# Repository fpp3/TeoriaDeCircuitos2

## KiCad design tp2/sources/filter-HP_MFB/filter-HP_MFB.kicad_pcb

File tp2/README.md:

# TC2 - Trabajo Práctico Nº 2: Caracterización de Filtro Activo (Sección 2.1.5)

Aplicación web interactiva y ultrarrápida diseñada específicamente para la toma de datos de laboratorio, cálculo automático de tolerancias/errores, trazado de curvas y exportación para el informe de la **Sección 2.1.5** del TP2 de **Teoría de Circuitos II (UTN FRC)**.

---

## 🚀 Cómo ejecutar la aplicación

Podés iniciarla con Python (abre el navegador automáticamente):

```bash
python3 run_app.py
```

O también podés abrir directamente en tu navegador el archivo:
```bash
app/index.html
```

> **Nota:** La aplicación es **100% offline y autónoma** (las librerías están incluidas localmente en `app/lib/`), por lo que podés usarla en el laboratorio sin conexión a internet ni WiFi.

---

## ⚡ Características principales

### 1. Pensada para mediciones de tensión sobre resistencias y puntos de prueba
Tal como se trabaja en el banco de laboratorio, **no hace falta abrir el circuito para intercalar un amperímetro**:
- **Entrada ($I_{in}$):** Se ingresa la caída de tensión medida sobre la resistencia de shunt de entrada ($V_{Rshunt,in}$), y la app calcula $I_{in} = \frac{V_{Rshunt,in}}{R_{shunt,in}}$.
- **Etapa 1 ($V_{E1}$):** Medición de tensión en la salida del restador (pin 8 de U1C) respecto a GND.
- **Etapa 2 ($V_{filtro}$):** Medición de tensión en la salida del Sallen-Key (pin 14 de U1D) respecto a GND.
- **Etapa 3 ($I_{out}$ hacia PLC):** Permite elegir cómo se midió la salida:
  1. *Caída sobre $R_{carga}$ ($V_{Rcarga}$):* $I_{out} = \frac{V_{Rcarga}}{R_{carga}}$ (Recomendado).
  2. *Tensión en colector de Q1 ($V_C$ a GND):* $V_{Rcarga} = V_{CC} - V_C \implies I_{out} = \frac{V_{Rcarga}}{R_{carga}}$.
  3. *Tensión en emisor de Q1 ($V_E$ sobre $R_{shunt,out}$):* $I_E = \frac{V_E}{R_{shunt,out}} \implies I_{out} = \alpha \cdot I_E$.
  4. *Medición directa con miliamperímetro* ($I_{out}$ en mA).

### 2. Calibración real de componentes
Permite ingresar los valores reales medidos con multímetro de:
- $R_{shunt,in}$ (nominal 250 $\Omega$)
- $R_{shunt,out}$ (nominal 250 $\Omega$)
- $R_{carga}$ (nominal 250 $\Omega$)
- $V_{CC}$ de fuente (nominal 24.0 V)
- $\beta$ estimado del transistor BC337 / 2N2222 (para evaluar el error teórico por corriente de base $\alpha = \frac{\beta}{\beta+1}$)

### 3. Caracterización Estática (Linealidad 4 a 20 mA)
- Puntos estándar de inyección: 4 mA, 8 mA, 12 mA, 16 mA y 20 mA (con posibilidad de agregar o quitar filas).
- Cálculo en tiempo real de errores relativos porcentuales de cada etapa.
- Regresión lineal por mínimos cuadrados ($I_{out} = m \cdot I_{in} + b$) y coeficiente $R^2$.
- Gráfico interactivo de la curva de transferencia $I_{out}$ vs $I_{in}$ superpuesto a la recta ideal.
- Gráfico de barras de distribución de errores por etapa.

### 4. Caracterización Dinámica (Bode 1 Hz a 100 Hz)
- Barrido de frecuencias con inyección senoidal + offset DC.
- Entrada de $V_{in}$ y $V_{out}$ (en $V_{pp}$ medidos con osciloscopio) y $\Delta t$ opcional para fase.
- Cálculo automático de ganancia $A_v$, magnitud en dB y comparación contra la curva teórica de Butterworth de 2º orden ($f_c = 10\text{ Hz}$):
  $$|H(jf)|_{\text{dB}} = -10 \log_{10}\left(1 + \left(\frac{f}{10}\right)^4\right)$$
- **Frecuencia de corte real a -3 dB:** Interpolación log-lineal automática del punto exacto donde la ganancia cruza $-3.01\text{ dB}$.
- **Atenuación exacta a 50 Hz:** Verificación del rechazo al ruido de red de 50 Hz (ideal $-27.97\text{ dB}$, atenuación $\sim 25\times$).
- **Pendiente asintótica (Roll-off):** Cálculo de la caída en dB/década en la banda de rechazo (ideal $-40\text{ dB/déc}$).
- Diagrama de Bode interactivo en escala logarítmica con curva teórica continua, marcadores experimentales y líneas guía.

### 5. Guardado, Carga y Exportación
- **Auto-guardado en LocalStorage:** Cualquier dato ingresado queda guardado automáticamente en el navegador; si recargás la página o cerrás la pestaña, nada se pierde.
- **Guardar / Cargar Sesión JSON:** Backup completo descargable en formato `.json` para archivar o compartir entre compañeros de grupo.
- **Exportación CSV:** Descarga directa de archivos `.csv` para procesar en Excel, Google Sheets, Python o MATLAB.
- **Generador de Tablas LaTeX:** Código fuente listo con formato `\begin{table}` y `tabular` para pegar en Overleaf.
- **Resumen Markdown:** Conclusiones y valores clave listos para el informe.
- **Exportación de Gráficos:** Botones para descargar las imágenes PNG en alta definición.
- **Botón "Cargar Demo":** Carga datos coherentes de simulación para verificar visualmente todo el funcionamiento.

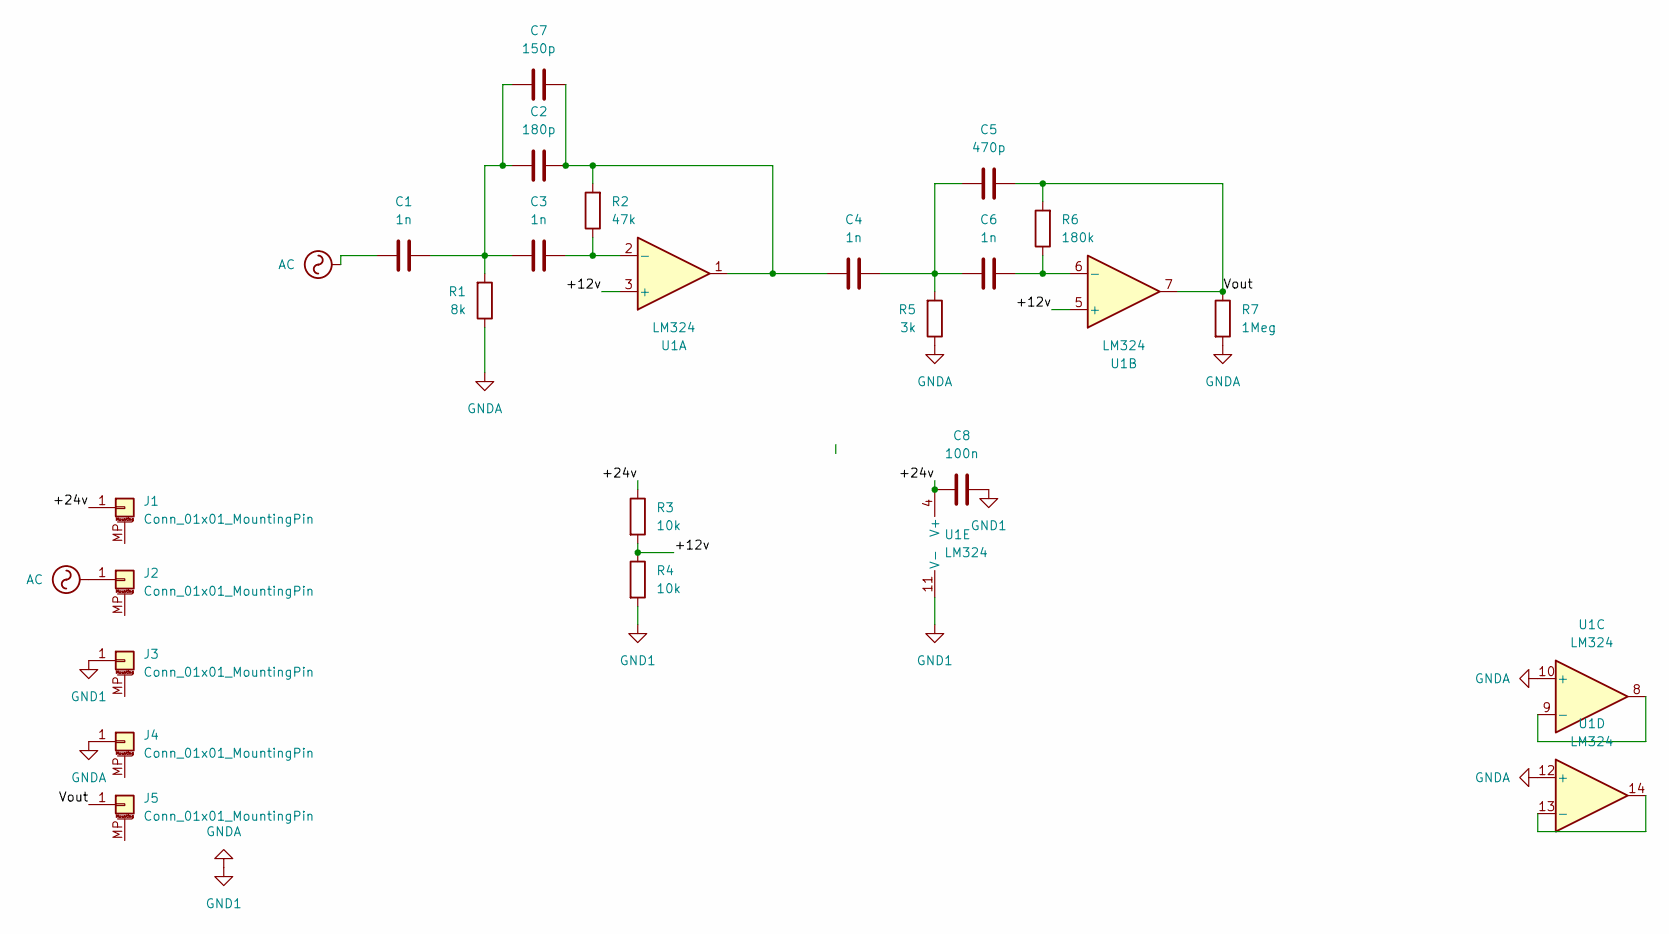
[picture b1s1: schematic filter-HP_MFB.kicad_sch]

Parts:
C1, C3, C4, C6: 1n; C_Disc_D5.0mm_W2.5mm_P5.00mm
C2: 180p; C_Disc_D5.0mm_W2.5mm_P5.00mm
C5: 470p; C_Disc_D5.0mm_W2.5mm_P5.00mm
C7: 150p; C_Disc_D5.0mm_W2.5mm_P5.00mm
C8: 100n; C_Disc_D5.0mm_W2.5mm_P5.00mm
J1, J2, J3, J4, J5: Conn_01x01_MountingPin; TestPoint_Pad_4.0x4.0mm
R1: 8k; R_Axial_DIN0207_L6.3mm_D2.5mm_P7.62mm_Horizontal
R2: 47k; R_Axial_DIN0207_L6.3mm_D2.5mm_P7.62mm_Horizontal
R3, R4: 10k; R_Axial_DIN0207_L6.3mm_D2.5mm_P7.62mm_Horizontal
R5: 3k; R_Axial_DIN0207_L6.3mm_D2.5mm_P7.62mm_Horizontal
R6: 180k; R_Axial_DIN0207_L6.3mm_D2.5mm_P7.62mm_Horizontal
R7: 1Meg; R_Axial_DIN0207_L6.3mm_D2.5mm_P7.62mm_Horizontal
U1: LM324; CERDIP-14_W7.62mm_SideBrazed_LongPads_Socket

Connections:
/+12v: R3.2, R4.1, U1.3 (+), U1.5 (+)
/+24v: C8.2, J1.1 (Pin_1_1), R3.1, U1.4 (V+)
/Vout: C5.1, J5.1 (Pin_1_1), R6.2, R7.1, U1.7
AC: C1.2, J2.1 (Pin_1_1)
GND1: C8.1, J3.1 (Pin_1_1), J4.1 (Pin_1_1), R1.1, R4.2, R5.1, R7.2, U1.10 (+), U1.11 (V-), U1.12 (+)
unnamed: C1.1, C2.2, C3.2, C7.2, R1.2
unnamed: C2.1, C4.2, C7.1, R2.2, U1.1
unnamed: C4.1, C5.2, C6.2, R5.2
unnamed: C3.1, R2.1, U1.2 (-)
unnamed: C6.1, R6.1, U1.6 (-)
unnamed: U1.8, U1.9 (-)
unnamed: U1.13 (-), U1.14

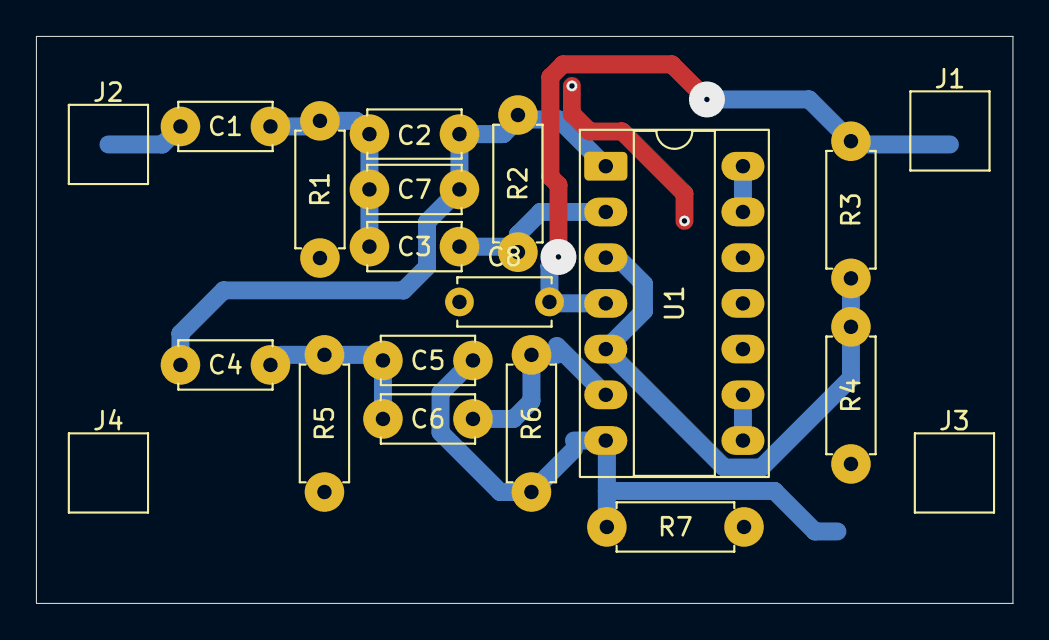
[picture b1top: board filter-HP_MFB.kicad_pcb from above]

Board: 2 copper layers, 54.2 x 31.5 mm, 21 parts (1 on the bottom side), 12 nets.

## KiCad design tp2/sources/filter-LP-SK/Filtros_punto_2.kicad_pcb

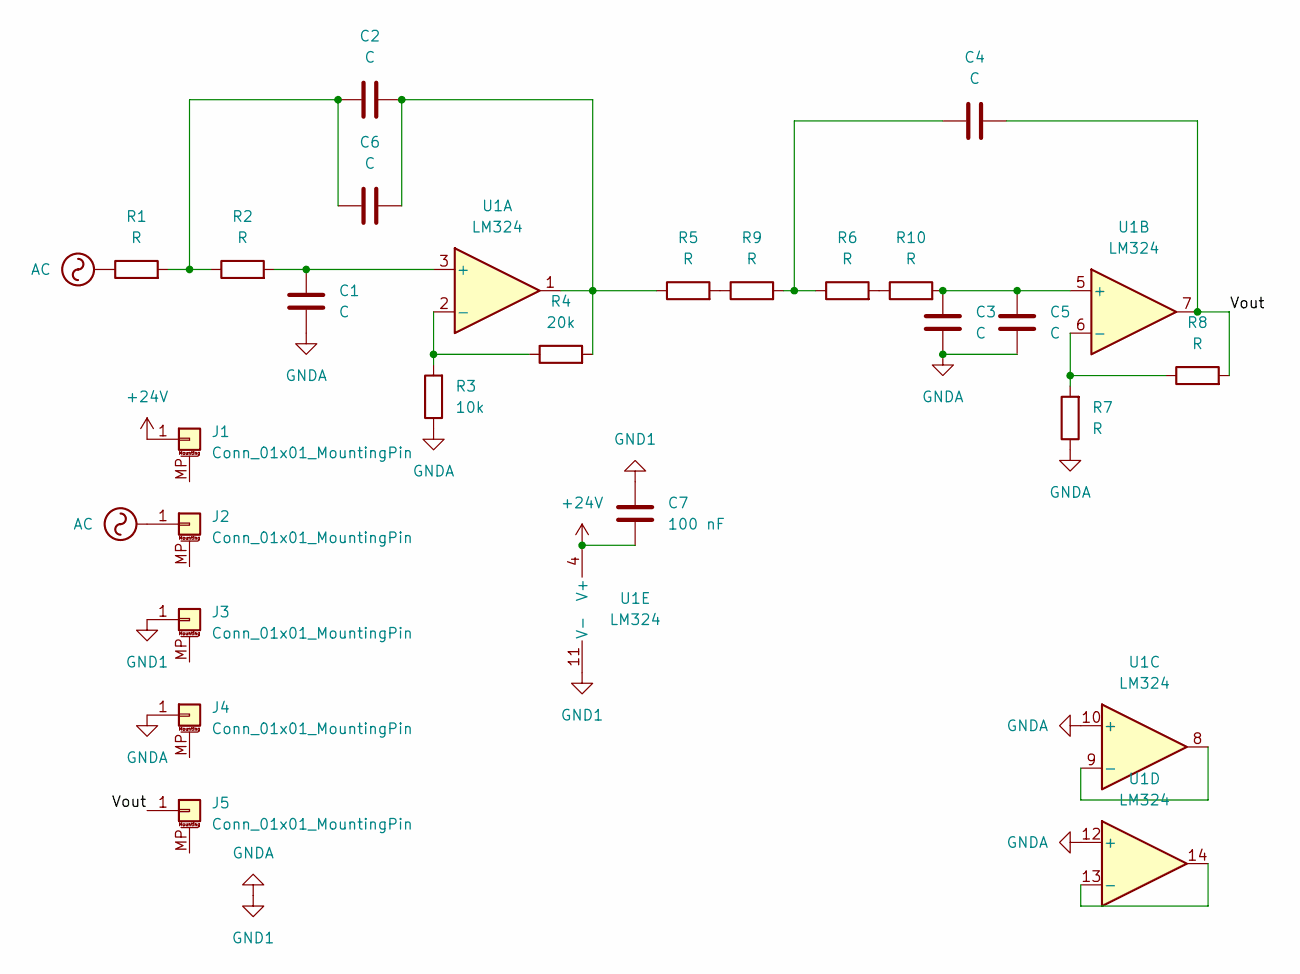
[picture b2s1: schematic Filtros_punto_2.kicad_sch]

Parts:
C1, C2, C3, C4, C5, C6: C; C_Disc_D5.0mm_W2.5mm_P5.00mm
C7: 100 nF; C_Disc_D5.0mm_W2.5mm_P5.00mm
J1, J2, J3, J4, J5: Conn_01x01_MountingPin; TestPoint_Pad_4.0x4.0mm
R1, R2, R5, R6, R7, R8, R9, R10: R; R_Axial_DIN0207_L6.3mm_D2.5mm_P7.62mm_Horizontal
R3: 10k; R_Axial_DIN0207_L6.3mm_D2.5mm_P7.62mm_Horizontal
R4: 20k; R_Axial_DIN0207_L6.3mm_D2.5mm_P7.62mm_Horizontal
U1: LM324; CERDIP-14_W7.62mm_SideBrazed_LongPads_Socket

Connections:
+24V: C7.2, J1.1 (Pin_1_1), U1.4 (V+)
/Vout: C4.1, J5.1 (Pin_1_1), R8.2, U1.7
AC: J2.1 (Pin_1_1), R1.1
GND1: C1.2, C3.2, C5.2, C7.1, J3.1 (Pin_1_1), J4.1 (Pin_1_1), R3.1, R7.1, U1.10 (+), U1.11 (V-), U1.12 (+)
unnamed: C2.1, C6.2, R4.2, R5.1, U1.1
unnamed: C2.2, C6.1, R1.2, R2.1
unnamed: C4.2, R6.1, R9.2
unnamed: R5.2, R9.1
unnamed: R6.2, R10.1
unnamed: C1.1, R2.2, U1.3 (+)
unnamed: R3.2, R4.1, U1.2 (-)
unnamed: C3.1, C5.1, R10.2, U1.5 (+)
unnamed: R7.2, R8.1, U1.6 (-)
unnamed: U1.8, U1.9 (-)
unnamed: U1.13 (-), U1.14

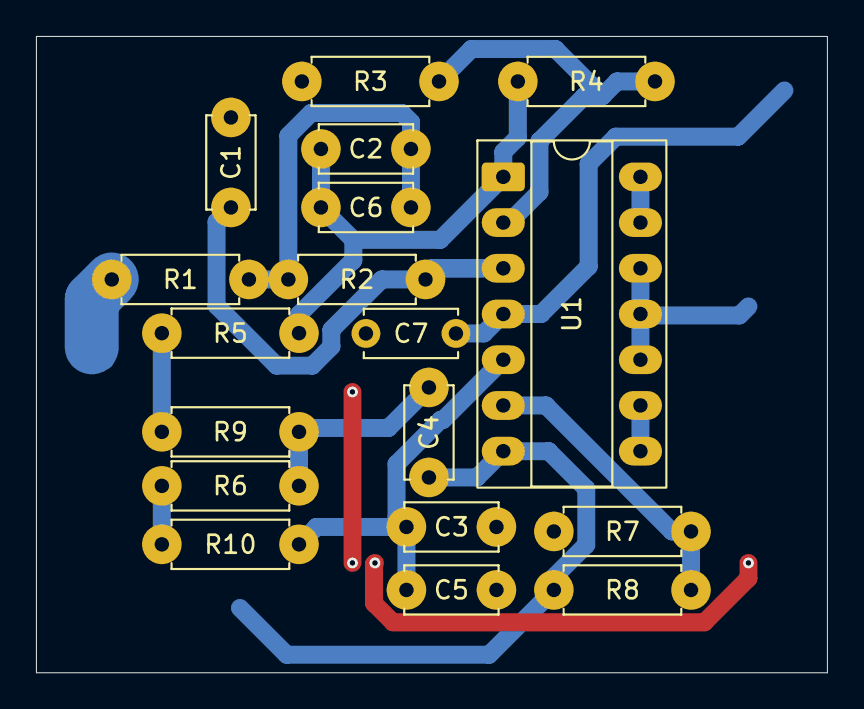
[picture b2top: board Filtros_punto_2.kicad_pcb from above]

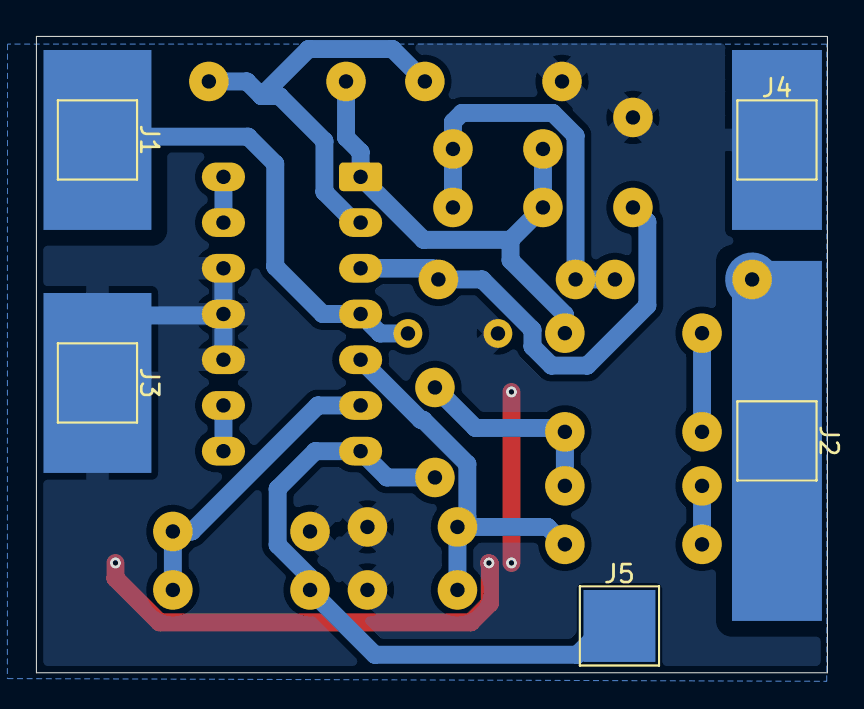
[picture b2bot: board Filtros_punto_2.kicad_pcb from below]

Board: 2 copper layers, 43.9 x 35.3 mm, 23 parts (5 on the bottom side), 15 nets.

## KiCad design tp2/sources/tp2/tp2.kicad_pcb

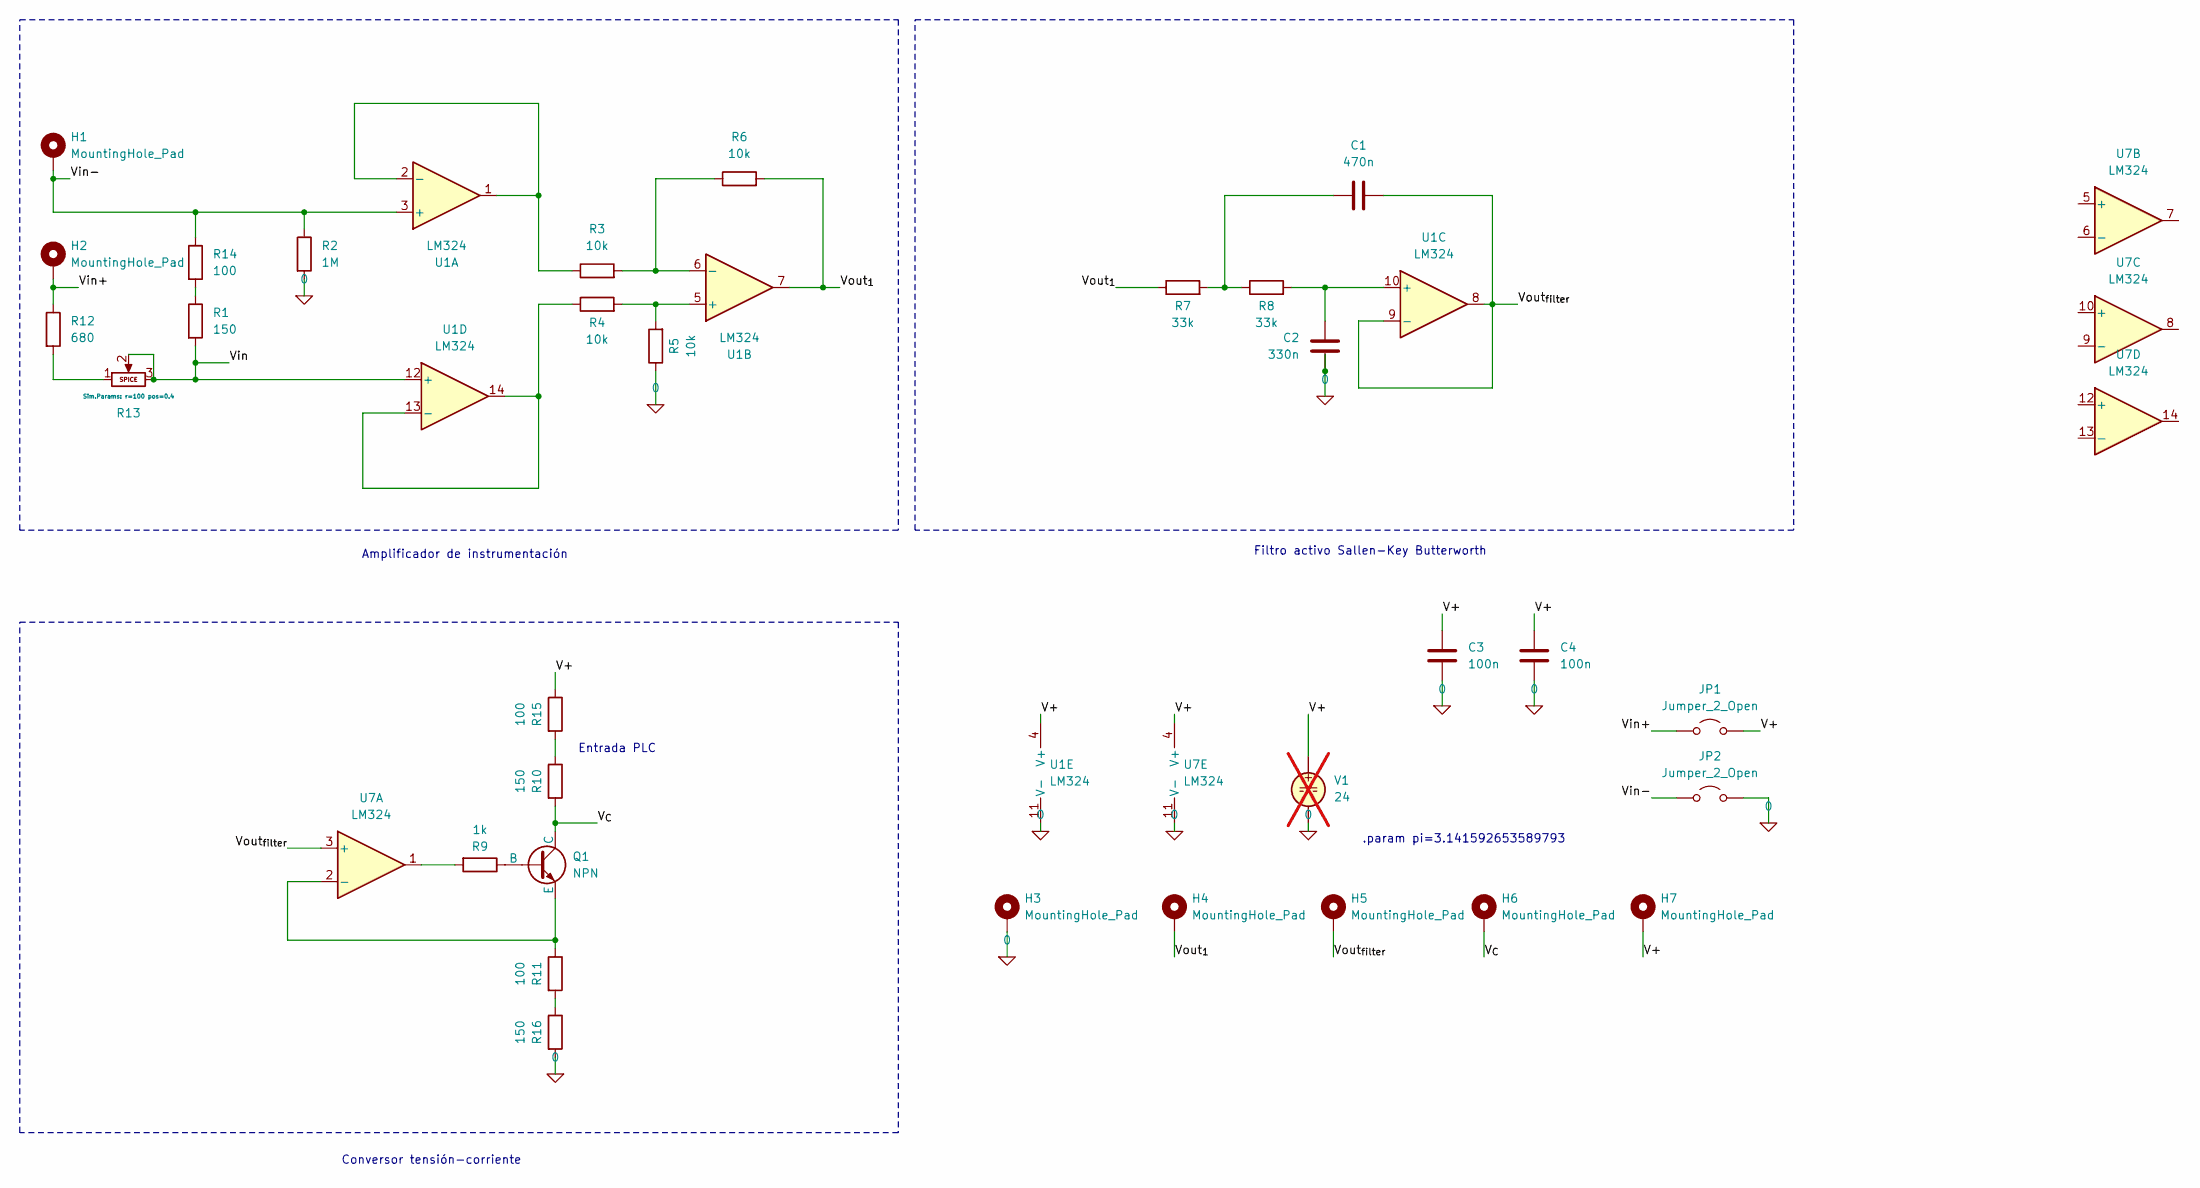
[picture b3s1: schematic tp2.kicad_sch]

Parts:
C1: 470n; C_Rect_L7.2mm_W2.5mm_P5.00mm
C2: 330n; C_Rect_L7.2mm_W2.5mm_P5.00mm
C3, C4: 100n; C_Disc_D6.0mm_W2.5mm_P5.00mm
H1, H2, H3, H4, H5, H6, H7: MountingHole_Pad; TestPoint_THTPad_2.0x2.0mm_Drill1.0mm
JP1, JP2: Jumper_2_Open; PinHeader_1x02_P2.54mm_Vertical
Q1: NPN; TO-92
R1, R10, R16: 150; R_Axial_DIN0207_L6.3mm_D2.5mm_P7.62mm_Horizontal
R2: 1M; R_Axial_DIN0207_L6.3mm_D2.5mm_P7.62mm_Horizontal
R3, R4, R5, R6: 10k; R_Axial_DIN0207_L6.3mm_D2.5mm_P7.62mm_Horizontal
R7, R8: 33k; R_Axial_DIN0207_L6.3mm_D2.5mm_P7.62mm_Horizontal
R9: 1k; R_Axial_DIN0207_L6.3mm_D2.5mm_P7.62mm_Horizontal
R11, R14, R15: 100; R_Axial_DIN0207_L6.3mm_D2.5mm_P7.62mm_Horizontal
R12: 680; R_Axial_DIN0207_L6.3mm_D2.5mm_P7.62mm_Horizontal
R13: Potentiometer; Potentiometer_Bourns_3266Y_Vertical
U1, U7: LM324; DIP-14_W7.62mm_Socket
V1: 24; not fitted

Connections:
0: C2.1, C3.2, C4.2, H3.1 (1_1), JP2.2 (B), R2.2, R5.1, R16.2, U1.11 (V-), U7.11 (V-), V1.2
/V+: C3.1, C4.1, H7.1 (1_1), JP1.2 (B), R15.1, U1.4 (V+), U7.4 (V+), V1.1
/V_{C}: H6.1 (1_1), Q1.1 (C), R10.2
/Vin: R1.2, R13.2, R13.3, U1.12 (+)
/Vin+: H2.1 (1_1), JP1.1 (A), R12.1
/Vin-: H1.1 (1_1), JP2.1 (A), R2.1, R14.1, U1.3 (+)
/Vout_{1}: H4.1 (1_1), R6.2, R7.1, U1.7
/Vout_{filter}: C1.2, H5.1 (1_1), U1.8, U1.9 (-), U7.3 (+)
unnamed: C1.1, R7.2, R8.1
unnamed: Q1.2 (B), R9.1
unnamed: Q1.3 (E), R11.1, U7.2 (-)
unnamed: R1.1, R14.2
unnamed: R9.2, U7.1
unnamed: R10.1, R15.2
unnamed: R11.2, R16.1
unnamed: R12.2, R13.1
unnamed: R3.1, U1.1, U1.2 (-)
unnamed: R4.2, R5.2, U1.5 (+)
unnamed: R3.2, R6.1, U1.6 (-)
unnamed: C2.2, R8.2, U1.10 (+)
unnamed: R4.1, U1.13 (-), U1.14

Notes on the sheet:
Entrada PLC
.param pi=3.141592653589793
Filtro activo Sallen-Key Butterworth
Conversor tensión-corriente
Amplificador de instrumentación

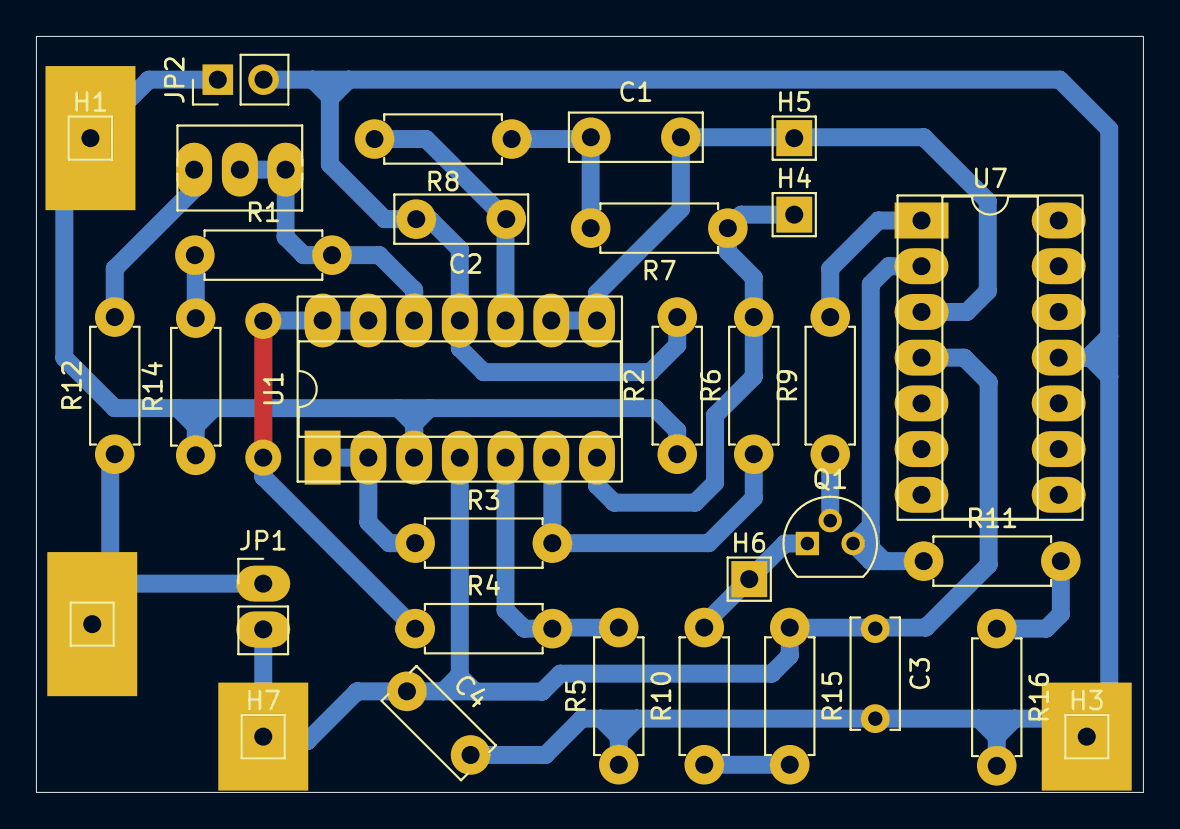
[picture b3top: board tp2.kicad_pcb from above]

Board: 2 copper layers, 61.5 x 42.0 mm, 32 parts (0 on the bottom side), 21 nets.

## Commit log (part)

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2026-05-30 tp1: Agrega consigna
2026-05-31 tp1: agrega desarrollo analitico ej1
2026-06-09 punto 2 finalizado
2026-06-10 punto 2 finalizado ahora si con todo corregido (creo)
2026-06-10 tp1: agrega placeholders para implementación
2026-06-18 tp1: agrega bode en hz ej3 y notas de ensayos en lab
2026-06-18 agregada implementacion EJ2
2026-06-19 tp1: agrega implementacion del ejercicio 1
2026-06-19 tp1: corrige gráficas de bodas ej3
2026-06-26 fin punto 2?
2026-06-26 tp1: Correcciones menores en desarrollo
2026-06-26 rayo desIAizador para el ej2
2026-06-26 ahora si desIAizado y agregadas herramientas de medicion en html
2026-06-26 tp1: termino parte ej3
2026-06-26 tp1: Correcciones de formato en implementacion
2026-06-27 tp1: Correcciones integrales
2026-06-27 ahora si fin delfin
2026-06-27 polos y ceros en Hz ej 2
2026-06-27 cambios finales
2026-06-27 FIN TP1
